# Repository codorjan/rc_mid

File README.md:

# SPI/Microwire Interface Designed For RC2014

This is an SPI/Microwire interface card designed for the RC2014 microcomputer system based upon National Semiconductor's TP3465 Microwire Interface Device. Its primary intent is to provide a reasonably fast interface to two SD cards in an RC2014 system, although it can potentially be used to communicate with up to four SPI devices with some limitations:

- only SPI modes 0 and 2 are supported (i.e. CPOL=0 or 1, CPHA=0)
- the maximum clock rate is 5 MHz

A version of [RomWBW](https://github.com/wwarthen/RomWBW) modified to drive this board is available in source form at https://github.com/codorjan/RomWBW/tree/mid with configuration RCZ80_mid.

## Build Notes

Until this is properly documented, refer to the [schematic](mid.pdf).

SD cards run at 3.3 volts but the RC2014 bus is 5 volts so it's expected an adapter with built-in level shifters will be used. Unfortunately there's no standard pinout so this board has footprints for three different MicroSD adapters: [Pololu](https://www.pololu.com/product/2587), [Adafruit](https://www.adafruit.com/product/254), and Catalex (labelled as 'EBAY' on the board as this is where they're most commonly found). Only the footprint(s) being used need to be populated, but note that the Catalex adapters always drive the MISO line so if one is used it must be the only device on the SPI bus.

Capacitors C1-C3 (100nF, MLCC) are power bypass/decoupling capacitors for each IC and C4 (10µF, electrolytic) provides additional transient decoupling for the TP3465 itself. R1-R5 (10kΩ) act as pull-ups for the chip select logic. R6 (100kΩ) is a pull-up for the MISO line as not all adapters provide one. (This is only useful if the Adafruit adapter is being used as the Pololu adapter already includes one and the Catalex adapter is constantly driving MISO. RomWBW already accounts for the lack of one in software so even on the Adafruit adapter it's probably unnecessary. If R6 is installed it can still be disabled by leaving jumper JP1 open.) R7 and R8 (100kΩ) are meant to either pull-up or pull-down the card detect lines for the two SD interfaces through JP2 and JP3, respectively. (These will probably be left off a future revision of this card: there doesn't seem to be any standard for whether card detect should be active high or active low, making use of these lines difficult. The Catalex adapter doesn't provide a card detect line at all. RomWBW doesn't use them even when they're available.)

The TP3465 has been discontinued but can be found on eBay or Utsource (these are likely used parts); the 28-pin PLCC package required by this card is listed as TP3465V.

## License

Copyright 2020 Chris Odorjan

This work is licensed under a [Creative Commons Attribution-ShareAlike 4.0 International License](http://creativecommons.org/licenses/by-sa/4.0/).

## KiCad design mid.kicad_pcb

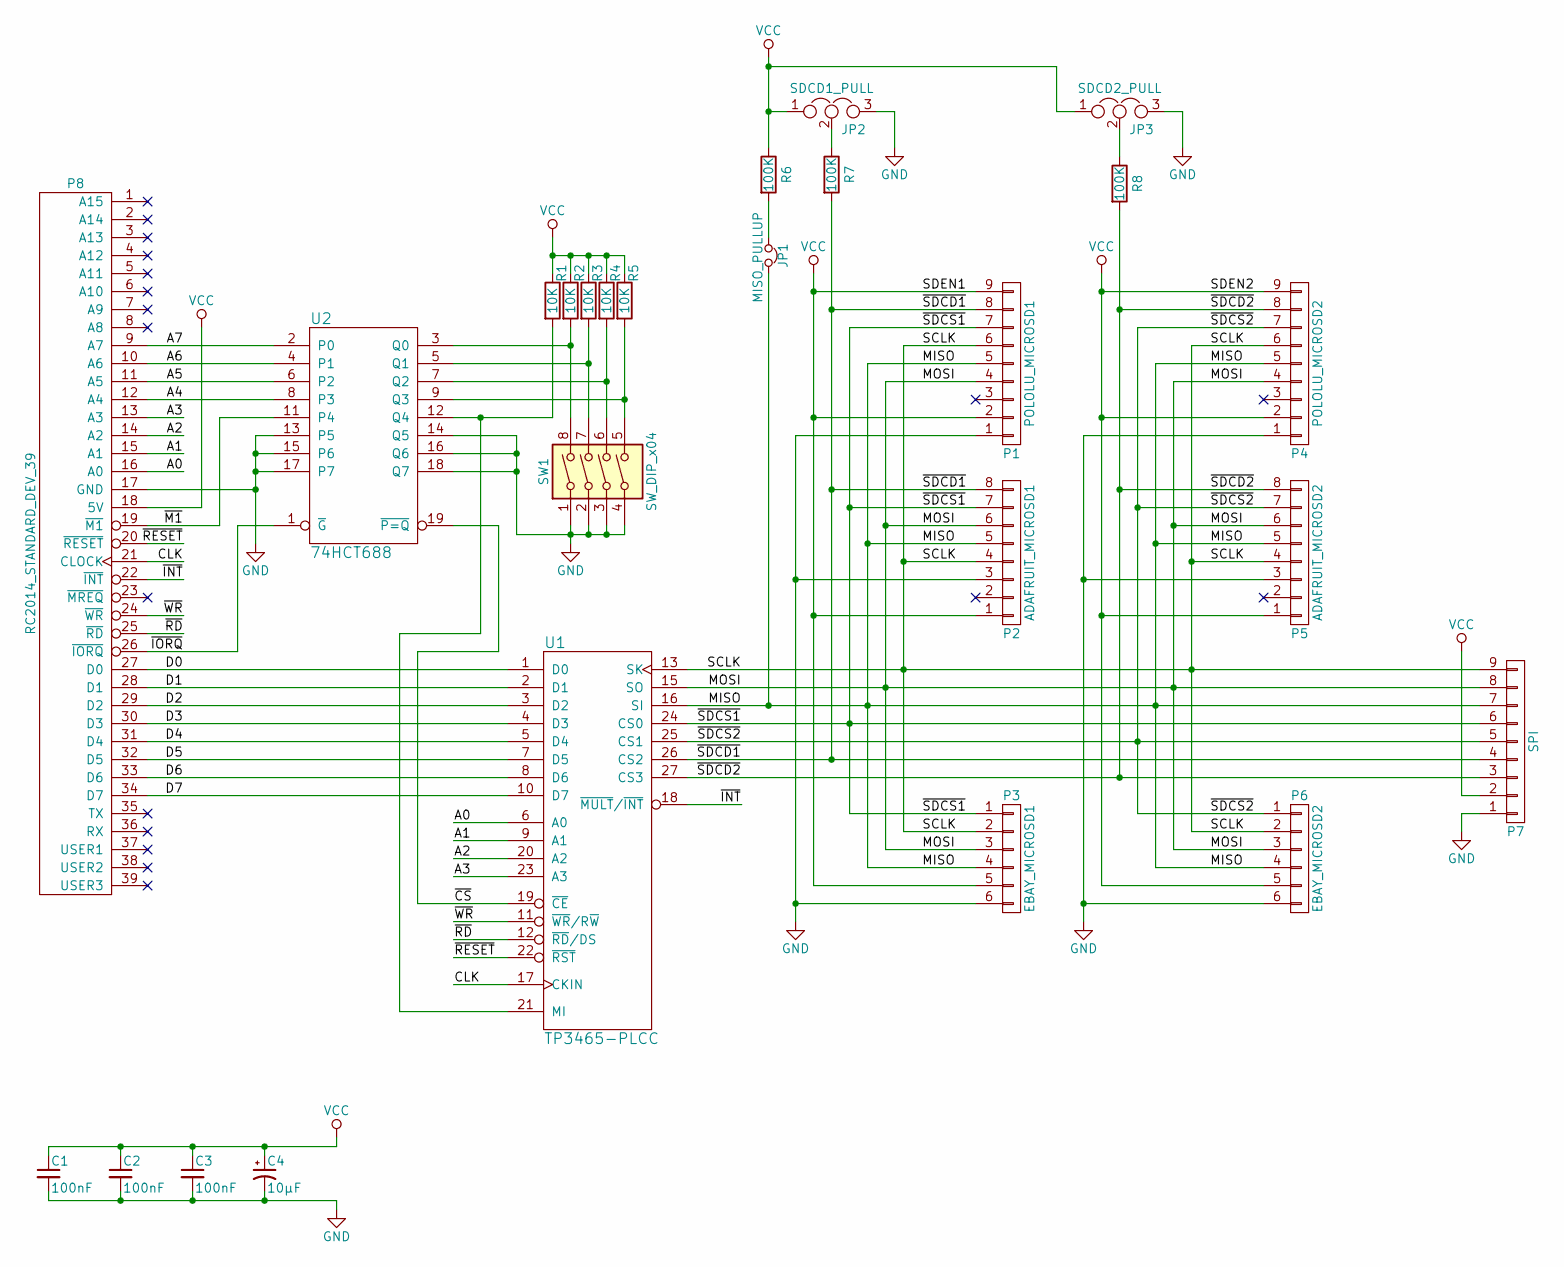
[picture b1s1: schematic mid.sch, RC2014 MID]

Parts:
C1, C2, C3: 100nF; C_Rect_L4.6mm_W2.0mm_P2.50mm_MKS02_FKP02
C4: 10µF; CP_Radial_D5.0mm_P2.00mm
JP1: MISO_PULLUP; PinHeader_1x02_P2.54mm_Vertical
JP2: SDCD1_PULL; PinHeader_1x03_P2.54mm_Vertical
JP3: SDCD2_PULL; PinHeader_1x03_P2.54mm_Vertical
P1: POLOLU_MICROSD1; PinHeader_1x09_P2.54mm_Vertical
P2: ADAFRUIT_MICROSD1; PinHeader_1x08_P2.54mm_Vertical
P3: EBAY_MICROSD1; PinHeader_1x06_P2.54mm_Vertical
P4: POLOLU_MICROSD2; PinHeader_1x09_P2.54mm_Vertical
P5: ADAFRUIT_MICROSD2; PinHeader_1x08_P2.54mm_Vertical
P6: EBAY_MICROSD2; PinHeader_1x06_P2.54mm_Vertical
P7: SPI; PinHeader_1x09_P2.54mm_Vertical
P8: RC2014_STANDARD_DEV_39; PinHeader_1x39_P2.54mm_Vertical
R1, R2, R3, R4, R5: 10K; R_Axial_DIN0207_L6.3mm_D2.5mm_P7.62mm_Horizontal
R6, R7, R8: 100K; R_Axial_DIN0207_L6.3mm_D2.5mm_P7.62mm_Horizontal
SW1: SW_DIP_x04; SW_DIP_SPSTx04_Piano_CTS_Series194-4MSTN_W7.62mm_P2.54mm
U1: TP3465-PLCC; PLCC-28_THT-Socket
U2: 74HCT688; DIP-20_W7.62mm_Socket

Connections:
/A0: P8.16 (A0), U1.6 (A0)
/A1: P8.15 (A1), U1.9 (A1)
/A2: P8.14 (A2), U1.20 (A2)
/A3: P8.13 (A3), U1.23 (A3)
/A4: P8.12 (A4), U2.8 (P3)
/A5: P8.11 (A5), U2.6 (P2)
/A6: P8.10 (A6), U2.4 (P1)
/A7: P8.9 (A7), U2.2 (P0)
/CLK: P8.21 (CLOCK), U1.17 (CKIN)
/D0: P8.27 (D0), U1.1 (D0)
/D1: P8.28 (D1), U1.2 (D1)
/D2: P8.29 (D2), U1.3 (D2)
/D3: P8.30 (D3), U1.4 (D3)
/D4: P8.31 (D4), U1.5 (D4)
/D5: P8.32 (D5), U1.7 (D5)
/D6: P8.33 (D6), U1.8 (D6)
/D7: P8.34 (D7), U1.10 (D7)
/MISO: JP1.2, P1.5, P2.5, P3.4, P4.5, P5.5, P6.4, P7.7, U1.16 (SI)
/MOSI: P1.4, P2.6, P3.3, P4.4, P5.6, P6.3, P7.8, U1.15 (SO)
/SCLK: P1.6, P2.4, P3.2, P4.6, P5.4, P6.2, P7.9, U1.13 (SK)
/~CS: U1.19 (~CE), U2.19 (~P=Q)
/~INT: P8.22 (~INT), U1.18 (~MULT~/~INT)
/~IORQ: P8.26 (~IORQ), U2.1 (~G)
/~M1: P8.19 (~M1), U2.11 (P4)
/~RD: P8.25 (~RD), U1.12 (~RD~/DS)
/~RESET: P8.20 (~RESET), U1.22 (~RST)
/~SDCD1: P1.8, P2.8, P7.4, R7.2, U1.26 (CS2)
/~SDCD2: P4.8, P5.8, P7.3, R8.2, U1.27 (CS3)
/~SDCS1: P1.7, P2.7, P3.1, P7.6, U1.24 (CS0)
/~SDCS2: P4.7, P5.7, P6.1, P7.5, U1.25 (CS1)
/~WR: P8.24 (~WR), U1.11 (~WR~/R~W)
GND: C1.2, C2.2, C3.2, C4.2, JP2.3, JP3.3, P1.1, P2.3, P3.6, P4.1, P5.3, P6.6, P7.1, P8.17 (GND), SW1.1, SW1.2, SW1.3, SW1.4, U1.14 (GND), U2.10 (GND), U2.13 (P5), U2.14 (Q5), U2.15 (P6), U2.16 (Q6), U2.17 (P7), U2.18 (Q7)
unnamed: JP1.1, R6.2
unnamed: JP2.2, R7.1
unnamed: JP3.2, R8.1
unnamed: R1.2, U1.21 (MI), U2.12 (Q4)
unnamed: R2.2, SW1.8, U2.3 (Q0)
unnamed: R3.2, SW1.7, U2.5 (Q1)
unnamed: R4.2, SW1.6, U2.7 (Q2)
unnamed: R5.2, SW1.5, U2.9 (Q3)
VCC: C1.1, C2.1, C3.1, C4.1, JP2.1, JP3.1, P1.2, P1.9, P2.1, P3.5, P4.2, P4.9, P5.1, P6.5, P7.2, P8.18 (5V), R1.1, R2.1, R3.1, R4.1, R5.1, R6.1, U1.28 (VCC), U2.20 (VCC)

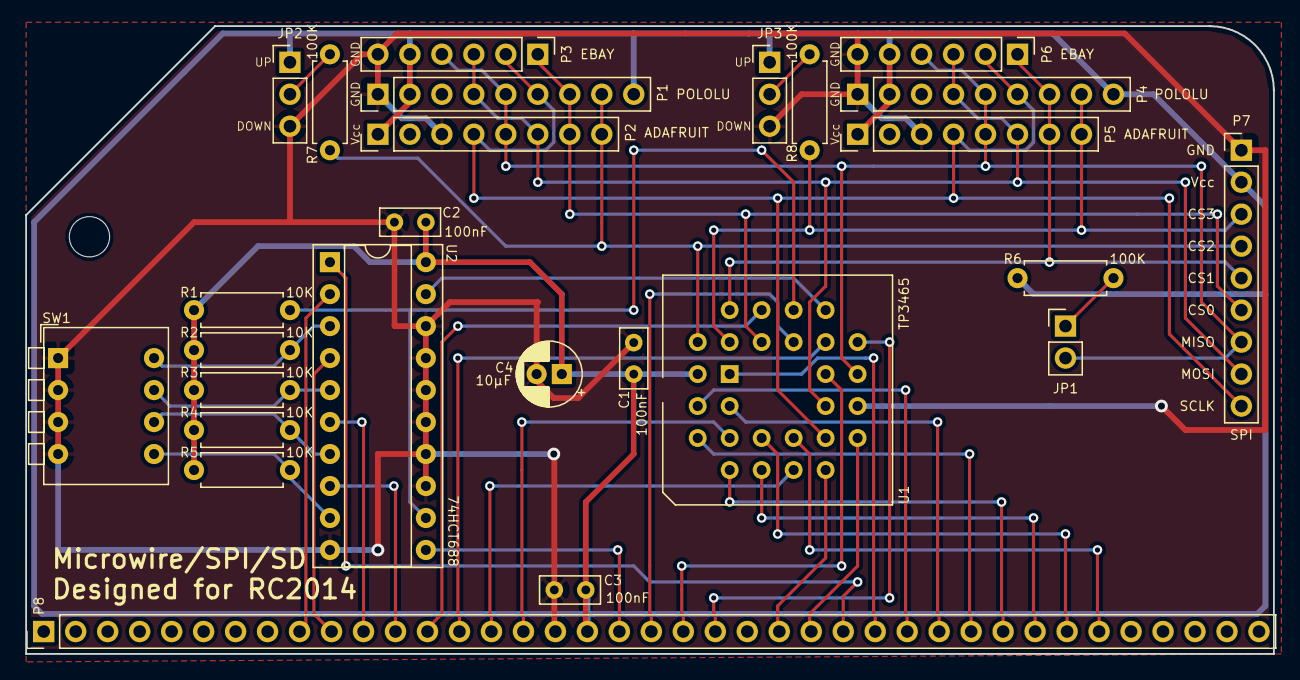
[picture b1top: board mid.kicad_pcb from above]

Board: 2 copper layers, 99.1 x 49.9 mm, 26 parts (0 on the bottom side), 41 nets.

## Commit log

2020-04-07 add CC-BY-SA-4.0 license
2020-04-07 add PCB
2020-04-11 adjust position of R8 & JP3 allows GND and VCC to be moved away from the top edge of the board
2020-04-21 switch pull-ups to 100K
2020-04-21 add silkscreen layers
2020-04-21 oop, forgot net file
2020-04-21 add gerbers
2020-05-13 add datasheet
2020-06-01 begin documentation
2020-06-01 add image and schematic along with description of components
2020-06-07 mention RomWBW tree and sources of TP3465V

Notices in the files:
mid.kicad_pcb:
©2020 Chris Odorjan
